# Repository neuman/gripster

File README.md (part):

# Gripster

**A wireless split thumb keyboard that turns your phone into a handheld deck.** Your phone clamps
landscape in the middle on a spring-loaded expanding bridge (Kishi/Backbone style, fits 130–170 mm
phones); two grips flank it and you thumb-type a real 78-key QWERTY on metal snap domes over Bluetooth.

<sub>☝️ **This image is a link — click it to spin the real assembly in 3D, pull it apart with the explode slider, and read the build story.**</sub>

> **Naming, once, so nothing is confusing later:** the project is called **Gripster** in prose. Every
> *internal* identifier — the ZMK board id `thumbdeck`, the board files `thumbdeck_right.kicad_pcb` /
> `thumbdeck_left.kicad_pcb`, the firmware artifact `thumbdeck-zmk.uf2`, the footprint library
> `thumbdeck.pretty/`, and the Bluetooth device name your phone will actually show — is
> **`thumbdeck`**. Those are real strings in real files and they stay as they are.

**What makes this interesting:**

- **It fits your phone, not one phone.** The grips ride a **2-part telescoping tray** (v0.24,
  Abxylute/8BitDo-style): stretch it open, drop the phone in, and two springs clamp it by the short
  edges — ~130 to ~170 mm long, and it collapses flat for a pocket. The phone is held **mechanically** —
  trapped between the tray and **soft TPU grippers with deep capture lips** — so it stays put even
  screen-down over your face like a Switch. **No magnets at all** — v0.25 dropped the secondary MagSafe
  ring: with the spring clamp, the toothed TPU grippers and the deep capture lips all doing their job it
  earned nothing, and its recess was the last thing wanting space in the moving jaw's travel.
- **The back is one flat plane.** v0.25 removed the v0.23 faceted crown and dropped both grips' backs
  to the tray floor, so the grips and the centre tray are coplanar — the device sits flat instead of
  rocking on its tray, and the back halves print straight on the bed with no supports. Every outside
  edge the hands wrap gets a 1.2 mm quarter-round.
- **No switches, no hand-soldering.** 78 Snaptron 7 mm metal snap domes press directly onto gold
  ENIG pads. Every soldered part is SMT on one side of each board — v0.21's pointing nub is a
  single SOT-23-6 hall sensor on the same reflow pass — so JLCPCB builds it 100 % turnkey,
  zero soldering by you.
- **It's not a split.** One certified nRF52840 module in the right grip scans a single 9×10 matrix;
  the left grip carries no active parts, joined by one **20-way** FFC ribbon that carries the matrix
  **and** the cell (v0.27 — the separate battery cable is deleted, so exactly one thing crosses the
  spine). One BLE device, no half-to-half pairing, one battery, one firmware image.
- **The whole product is generated from one Python file.**
  [`hardware/scripts/deck.py`](hardware/scripts/deck.py) emits the KiCad boards, the CadQuery
  shells, the renders *and* the ZMK keymap — so key openings land on dome pads by construction, not
  by luck.
- **The boards are real and finished.** Both PCBs are fully autorouted and DRC-clean in KiCad 9
  (0 violations, 0 unconnected), with the JLCPCB gerber + BOM + CPL package exporting cleanly.

> ### ⚠️ Honest status: designed, not built
>
> **No physical Gripster has ever existed.** Every image *of this device* is a render or a generated
> layout — the only photographs in the repo are of the Rii i8+ that was studied as a reference
> ([`references/`](references/)), alongside the original hand drawings in [`sketches/`](sketches/).
> rev-A (v0.27) is complete on paper: both boards routed and DRC-clean, the fab package
> exports cleanly, all 10 printed parts watertight and bed-fit-checked for an Ender 3 V2. (CI is
> stale — re-run it; the last green build predates the nub module.) Nothing has been ordered, printed, pressed, flashed or typed on.
>
> **Unmeasured and unknown:** ergonomics, dome feel and dome life, BLE range with a phone
> centimetres away and a hand around the antenna, real battery life, and every print tolerance.
> "0 DRC violations" means *no rule was broken*, not *the circuit is correct*.
>
> If you build one, **you are building the first one**. Read
> [Project status & roadmap](#project-status--roadmap) before you spend money.

---

## Table of contents

- [What is this?](#what-is-this)
- [Where to start](#where-to-start)
  - [What's in the repo](#whats-in-the-repo)
  - [Which doc answers which question](#which-doc-answers-which-question)
- [Project status & roadmap](#project-status--roadmap)
  - [Done](#done) · [Not done](#not-done--read-this-before-spending-money) · [Roadmap](#roadmap) · [Open design calls](#open-design-calls) · [Version history](#version-history)
- [FAQ](#faq)
- [Hardware](#hardware)
  - [At a glance](#at-a-glance)
  - [Why a module, not chip-down](#why-a-module-not-chip-down)
  - [Per-grip layout](#per-grip-layout)
  - [The boards, as routed](#the-boards-as-routed)
  - [The 3D model — printable shells + keymats](#the-3d-model--printable-shells--keymats)
  - [Parts list (BOM)](#parts-list-bom)
- [Firmware & software](#firmware--software)
  - [How it works — matrix, GPIO, power, antenna](#how-it-works--matrix-gpio-power-antenna)
  - [Building the firmware](#building-the-firmware)
- [Build guide](#build-guide)
- [Design & generation (the parametric model)](#design--generation-the-parametric-model)
  - [Fabrication view + real KiCad boards](#fabrication-view--real-kicad-boards)
  - [Reproduce the design](#reproduce-the-design)
- [Contributing](#contributing)
- [License](#license)

---

## What is this?

Phones are the most capable computer most people carry and the worst thing to type on. Gripster is a
handheld shell that fixes the input half without replacing the phone: your phone stays the screen
and the compute, and the deck around it becomes the keyboard.

The phone mounts **landscape in the centre**, clamped by two springs against toothed TPU grippers, and it
sits **down inside a well** — deep enough that the glass and the keyboard face form a single flat
plane 14.7 mm off the back. Two contoured grips flank it. You hold it like a game controller and
thumb-type a full split QWERTY: 78 keys on **metal snap domes**, the same clicky stainless discs used
in TV remotes and the [Rii i8+](references/rii8_ref.png), pressed straight onto gold pads on the PCB.
There is no switch, no stem, no solder — the dome *is* the switch. The whole thing takes its design
language from a Game Boy Color: boxy rounded outline, translucent Atomic-Purple shell, dark-gray
keymats. The original concept drawings are in [`sketches/`](sketches/).

Despite the two halves, **this is not a split keyboard**. One certified nRF52840 module lives in the
right grip and scans everything; the left grip holds no active silicon at all — domes, diodes, the
bridge connector, and (v0.27) the cell's plug and its fuse.

```
  LEFT grip (passive)                        RIGHT grip (MCU)
  42 domes + diodes  ── 20-way FFC jumper ──  Ebyte E73 (nRF52840)  ⇄ phone (BLE HID)
  D-pad/OK, mouse       straight type-A       + charger + USB-C + power switch
  LiPo + J4 + F1 PTC    14 matrix + VBAT      scans the whole 9×10 matrix
  (no chip)             + GND, one cable      charges over the same ribbon
```

That means one Bluetooth device to pair, no half-to-half link to drop, one battery to charge, and one
firmware image. The cost is a ribbon cable running through the spine under the phone well — since
**v0.27** that ribbon is 20-way and carries the raw cell alongside the matrix, so it is the *only*
thing crossing, and it is fused at the cell end (**F1**, a 0.75 A PPTC on the left board).

Everything you can see in this repo — the KiCad boards, the printable shells, the renders above, even
the ZMK keymap — is generated from a single parametric Python model,
[`hardware/scripts/deck.py`](hardware/scripts/deck.py). Move a key in the model and the board pad,
the shell opening, the keycap and the firmware matrix transform all move with it.

---

## Where to start

**Just browsing?** Open [the live site](https://neuman.github.io/gripster/) — spin the
model, drag the explode slider, tap the hotspots — then skim [At a glance](#at-a-glance) and the
[FAQ](#faq).

**Thinking about building one?** Read [Project status & roadmap](#project-status--roadmap) first — it
will either talk you out of it or tell you exactly what you are signing up for — then
[`docs/assembly.md`](docs/assembly.md) and
[`docs/fabrication-sourcing.md`](docs/fabrication-sourcing.md).

**Here for the engineering?** [Fabrication view + real KiCad boards](#fabrication-view--real-kicad-boards),
[`docs/routing-status.md`](docs/routing-status.md) and
[`docs/design-decisions.md`](docs/design-decisions.md).

### What's in the repo

| Directory | What's in it |
|---|---|
| [`hardware/scripts/`](hardware/scripts/) | **The source of truth.** [`deck.py`](hardware/scripts/deck.py) is the parametric model; the rest generate boards, fab output, firmware, simulations and 2D renders from it. Old 50-key experiments are archived in [`legacy/`](hardware/scripts/legacy/). |
| [`hardware/kicad/`](hardware/kicad/) | The generated KiCad 9 boards. Nothing here is hand-drawn — see its [README](hardware/kicad/README.md). The JLCPCB fab package builds into `generated/fab/` (a local build artifact, not committed). |
| [`hardware/cad/`](hardware/cad/) | CadQuery 3D: [`deck3d.py`](hardware/cad/deck3d.py) builds the shells and keymats, [`export_full_asm.py`](hardware/cad/export_full_asm.py) builds the nested GLB. Watertight STLs live in [`models/`](hardware/cad/models/). |
| [`hardware/footprints/`](hardware/footprints/) | Custom KiCad footprints, including the [snap-dome contact pad](hardware/footprints/snaptron_7mm_contact_pad.kicad_mod). Some are vendored third-party — see [License](#license). |
| [`hardware/layout/`](hardware/layout/) | [`keymat.json`](hardware/layout/keymat.json), the original sketch digitization. Historical only; the live layout is the `LEGENDS` tables in `deck.py`. |
| [`firmware/zmk-config/`](firmware/zmk-config/) | ZMK v0.3.0 config with a real board definition ([`config/boards/arm/thumbdeck/`](firmware/zmk-config/config/boards/arm/thumbdeck/)) — a unibody board, not a shield, not a split. |
| [`docs/`](docs/) | Eleven engineering documents, plus [`docs/diagrams/`](docs/diagrams/). Table below. |
| [`renders/`](renders/) | Every image in this README, all generated — CAD isometrics from `deck3d.py`, board renders from the `.kicad_pcb`s, and the two hero shots captured from the live viewer. [`history/`](renders/history/) keeps the superseded iteration log. |
| [`sketches/`](sketches/) · [`references/`](references/) | The original concept drawings, and Rii i8+ reference photos used during the design. |
| [`.github/workflows/`](.github/workflows/) | The self-contained ZMK build that produces `thumbdeck-zmk.uf2`. |

### Which doc answers which question

| I want to know… | Read |
|---|---|
| Why is it built this way? Every decision, with rejected alternatives | [`docs/design-decisions.md`](docs/design-decisions.md) |
| How do I actually assemble one, in order, without bricking it? | [`docs/assembly.md`](docs/assembly.md) |
| What do I buy, from whom, for how much? | [`docs/fabrication-sourcing.md`](docs/fabrication-sourcing.md) · [`docs/bill-of-materials.md`](docs/bill-of-materials.md) |
| How does the 9×10 matrix work, and why one diode per key? | [`docs/matrix-and-diodes.md`](docs/matrix-and-diodes.md) |
| Battery, charging, USB, ESD, the FFC bridge | [`docs/connectivity-and-power.md`](docs/connectivity-and-power.md) |
| How does a Python file turn into a routed PCB? | [`docs/routing-status.md`](docs/routing-status.md) |
| How does a Python file turn into printable shells? | [`docs/cad-process.md`](docs/cad-process.md) |
| What would an EE tear apart in a review? | [`docs/design-review.md`](docs/design-review.md) · [`docs/evaluation.md`](docs/evaluation.md) |
| What did we learn from cutting up a Rii i8+? | [`docs/reference-notes.md`](docs/reference-notes.md) |
| What does the architecture look like as a diagram? | [`docs/diagrams/`](docs/diagrams/) |

---

## Project status & roadmap

**rev-A (v0.27). Designed to the point of being orderable. Never built.**

### Done

| | |
|---|---|
| Both PCBs | Fully placed and **autorouted**, **0 DRC violations / 0 unconnected items** (KiCad 9, `kicad-cli 9.0.9`, error severity; both boards re-routed and re-verified for **v0.27**'s 20-way bridge, in the same commit that regenerated them — right board 75 nets / 114 footprints / 30 GND escape vias, left board 60 nets) |
| Fab package | 4-layer gerbers + JLC-format BOM + CPL export cleanly to `hardware/kicad/generated/fab/` via `gen_fab.py`; the exporter refuses to run unless DRC is clean. (That directory is a build artifact and is **not committed** — regenerate it, see [Reproduce the design](#reproduce-the-design).) |
| BOM | Every part real, LCSC-stocked and machine-placeable; no hand-soldered components |
| 3D | 221 bodies assembled and collision-checked at **every clamp position** (`deck3d.py --check` → 0 impossible overlaps at 130 / nominal / 170 / 179 mm open, cable enclosure sealed at each); all 6 shell parts (incl. the v0.21 nub spring + cap) + 2 TPU grippers + 2 keymats fit a 220 × 220 mm Ender 3 V2 bed (204 mm brim-safe limit) |
| Matrix proof | `sim_matrix.py` proves the full 78-key matrix is ghost-free with a diode per key |
| Firmware | Real ZMK v0.3.0 board definition; keymap and matrix transform generated from the model. CI last built green on 2026-07-15, **before the v0.21 nub module — re-run the workflow to validate the current design**. Never flashed; no hardware exists. |

### Not done — read this before spending money

| | |
|---|---|
| **Physically built** | **Never.** Zero boards ordered, zero shells printed, zero domes pressed, zero flashes. Every image of the device is a render. |
| Ergonomics | The grip shape, key pitch and thumb reach have never been tested by a human hand. v0.19 already reshaped the grips once on print-test feedback — expect more. |
| Dome feel & life | Snaptron force curve, keymat living-hinge fatigue and dome retention are *specified* but unmeasured. Fatigue-test a 3×3 keymat coupon before printing a full one. |
| Circuit correctness | Autorouted and DRC-clean is not the same as reviewed. No board has been powered, and no net has been probed. |
| RF | The antenna sits centimetres from a phone and inside a closing hand. Range loss is expected and unquantified. |
| Battery life | Never measured. The ~450–500 mAh cell and ZMK's sleep behaviour suggest weeks of light use; treat that as an estimate, not a spec. |
| Tolerances | Boss travel, screw-boss fit and lid gaps have only been checked in CAD, never against a real print. |
| **FFC route into the ZIF** | **Built in v0.27**, after turning out never to have existed. With the ZIF slot facing the spine there was only **1.20 mm of x** between the slot and a solid grip wall in which to lose **6.74 mm of z** — no route, in any version, for either cable, because both were drawn as straight boxes reaching neither connector. J2 now faces **inboard**: the ribbon folds in the grip's open back cavity and leaves through a low **stepped** duct (z −0.8 .. 2.6 on the grip side, .. 1.95 through the shroud so its roof keeps 1.42 mm) that passes *under* the phone-retention structure (all of which sits at z ≥ 3.9) rather than severing it. The descent clears the matrix diodes by **0.98 / 1.03 mm**, asserted against the real placement. `deck3d.py --check-lanes` sweeps the ribbon's full 21 mm section along the path and exits non-zero if any of it is buried. |

### Roadmap

1. **First article.** Order 5 sets, print the shells, build one, and write down everything that is
   wrong.
2. **Bring-up.** SWD-flash the bootloader, load the UF2, prove the matrix grip-by-grip, measure
   current draw and BLE range with a phone in the well and a hand on the grips.
3. **rev-B**, driven by whatever the first article teaches. Already parked for it: shoulder buttons,
   a canted/fanned key arc, and an I²C trackpad on the TP6–8 breakout.

### Open design calls

Decisions that are **yours to make** — they change the shape of the build:

1. **Feel.** Keys are **rectangular 8.5 × 7 mm at 10 × 9 mm pitch** (v0.17, i8+ chiclet — wider than
   tall so the 6-row field stays short). Still an open call: a flat ortho grid vs a **canted/fanned
   arc** to feel more like a controller — the arc is a keymat/standoff change, not a pitch change.
2. **Phone-fit window.** v0.24's expanding clamp fits phones with a **130–170 mm long edge** (cased)
   out of the box — the springs take up the rest. The jaw itself opens to **179 mm**: it has to
   clear the capture hooks to let the largest phone in, and v0.24e found that until then the travel
   was exactly the phone range, so a 170 mm phone couldn't physically be fitted. The nominal
   near-flush point is tuned to the
   **S25 Ultra + a 1.2 mm case**; `phone_span_min/max` (and `phone_t`/`case_t` for the recess depth)
   re-set the range and re-generate the shells (one command; boards unaffected).
3. **Cell size — settled in v0.18:** standard **403040 (~450–500 mAh)** in the left grip cavity (the
   only standard shape that fits the 5.1 mm free depth there); PROG's 196 mA ≈ 0.43 C suits it as-is.
   Sleep-managed runtime is still weeks.
4. **Shoulder buttons** for index fingers (offload thumb modifiers)? A rev-B matrix change.
5. **Trackpad** — dropped from v1 (single-maintainer ZMK driver + ATI tuning burden); the labelled
   I²C breakout (TP6–8) keeps a rev-B trackpad possible.

### Version history

<details>
<summary><strong>v0.16 → v0.20 changelog</strong> (click to expand)</summary>

- **v0.16 — the shell splits.** The one-piece shells (which needed a 350-class printer) become
  **five printed parts**: two back halves joined at mid-spine with printed tabs + wall shiplaps (no
  seam screws), two grip lids, and a screwed-on center panel that bridges the seam. Everything now
  prints flat on a 220 × 220 mm Ender 3 V2 bed.
- **v0.16-follow (2026-07-15).** A **Rii-style 2u Enter** ends the right grip's H-row — `H J K L +
  ENT`. The `'` key gave up its spot (`'` is now **FN+`;`**), bringing the total to **78 keys**. The
  right board was regenerated and rerouted (still 0/0), the fab package re-exported, **debossed
  keycap legends** added to the keymat model, and the shell screws modelled in the 3D assembly.
- **v0.17 — Rii proportions.** The grips take the Rii i8+'s proportions: **97 mm** tall, a chin cut,
  the E73 + entire power front-end moved up into the **top zone** (the old trackpad space) with the
  ceramic antenna pointing **up off the top board edge**, and **rectangular 8.5 × 7 mm keys** at
  10 × 9 mm pitch replacing the round ones. Boards became 79.5 × 97.0 mm.
- **v0.18 — the phone sinks.** A real **S25 Ultra in a thin case** drops into a **well in the center
  panel** so its **screen surface is flush with the lids' keyboard face** — one 14.7 mm-high front
  plane, and the device drops from 22.9 mm to **15.7 mm** thick overall. That left no cell height in
  the spine, so the **battery moved to the left grip's cavity**: a standard **403040 (~450–500 mAh)**
  under the passive PCB. No board change, no reroute. The FFC minimum length rose accordingly.
- **v0.19 — Game Boy Color rework.** From print-testing feedback: the grip outline goes
  **GBC-boxy** — the parabolic outer cheek bow is deleted (it blocked thumb reach to the
  edge-adjacent keys) and boards narrow **79.5 → 75.0 mm**; corners tuck to r8 (top, antenna-pinned)
  and r11 + a 1.0 mm **crown** (bottom). All 14 face screws become **M3×10 countersunk, flush with
  the face**. The phone well gets **closing end walls** (no more open slots into the grips) and the
  thumb scallop becomes a **watertight curved finger dish**. Shells render and export in
  **translucent Atomic Purple** with dark-gray keymats. Both boards re-routed from scratch against
  the new outline, still 0 violations / 0 unconnected.
- **v0.20 — mirrored modifiers.** A thumb can't cross the phone gap, so Ctrl/Shift/Alt now exist on
  **both** grips: two right-grip caps relabel (`AltGr`→`Alt`, the corner `\`→`Ctrl`) and both grips
  end in the identical stack — Ctrl at the bottom-outside corner, Shift above it, Alt beside Space.
  `\` and `|` move to **FN+`]` / FN+`[`** (direct bindings). Right grip emits RCTRL/RSHFT/RALT.
  **No sticky keys — all chords are plain holds.** Zero PCB change: the matrix transform regenerated
  byte-identical; keymats re-debossed; `sim_matrix` re-run — 78 keys, 0 collisions, PASS.

</details>

---

## FAQ

**Will it fit my phone?**
Out of the box, no — the well is dimensioned for a **Samsung S25 Ultra (77.6 × 162.8 × 8.2 mm bare)
in a ~1.2 mm thin case**, and the fit is tight by design because the screen has to sit flush. But the
phone is four numbers in the model (`phone_w`, `phone_h`, `phone_t`, `case_t` in
[`hardware/scripts/deck.py`](hardware/scripts/deck.py)); change them, re-run the 3D generator, and
you get shells for your phone. **The PCBs are unaffected** — only the printed parts change. Two
caveats: the grip separation is
derived straight from the cased phone envelope — a substantially **larger** phone pushes the grips
further apart than is comfortable to thumb-type across (a smaller one brings them closer, which is
fine ergonomically, you just get less screen). A large change also moves the FFC bridge connectors
apart, so re-check the ribbon length in [`docs/assembly.md`](docs/assembly.md) before ordering.

**Can I build one today?**
You can order everything today — the boards are routed, DRC-clean and the JLCPCB package exports with
one command. But you would be building the **first one that has ever existed**, and rev-A has never
been electrically or ergonomically validated. If that is appealing,
[`docs/assembly.md`](docs/assembly.md) is written to be followed literally, and the one thing to
check first is E73 module stock (JLC **C356849**) — it has been observed swinging from ~1000 units to
~20 in days.

**Is it a split keyboard?**
It looks like one and isn't. There is a **single 9×10 matrix** scanned by one MCU: the right grip
owns COL0–4 locally, the left grip's COL5–9 arrive over a **20-way** FFC ribbon (14 of its conductors
are the matrix and have not changed since rev-A; v0.27 put the battery on the spare ones), and all nine rows are
shared. In ZMK terms it's a **unibody board**, not `CONFIG_ZMK_SPLIT`. One device pairs to your
phone, one battery, one firmware. A useful debugging consequence: a dead **column** on the left
points at the ribbon; a dead **row** kills the same row on *both* grips.

**Why a module instead of a bare nRF52840?**
Because chip-down means owning a 2.4 GHz impedance match and VNA tuning, **FCC/IC/RED radiated
certification**, crystals, a USB bootloader and a from-scratch Zephyr board port. The Ebyte
E73-2G4M08S1C retires all of that, is stocked in JLCPCB's library so it machine-places, and still
breaks out far more GPIO than the 19 matrix pins + 1 battery ADC this design uses. Full reasoning in
[`docs/design-decisions.md`](docs/design-decisions.md) and
[below](#why-a-module-not-chip-down).

**Why no trackpad?**
It was designed in and then deliberately **cut from v1**: a maintained ZMK driver plus ATI/sensitivity
tuning is a large burden for a single maintainer, and it competed for the exact board area the module
and power front-end now occupy. Pointing since v0.21 is the right-grip **hall-effect nub**
(rate-control, ThinkPad-style) — which now lives on the very I²C breakout (**TP6–8**) that was
reserved for a rev-B trackpad — plus the left D-pad with FN-layer mouse keys as fallback. And the
user verdict behind the nub choice: trackpad-style thumb pointing means constantly lifting the
finger; a velocity-controlled nub doesn't.

**What's the battery life?**
Unknown — nothing has been measured. The design carries a standard **403040 LiPo (~450–500 mAh)** in
the left grip, charged at ~196 mA by an MCP73831, with battery percentage reported over BLE. A BLE HID
keyboard with a sleeping nRF52840 should give weeks of light use; that is an expectation based on
comparable ZMK builds, not a number from this device.

**Why ZMK and not QMK?**
ZMK is built around BLE and low-power sleep on nRF52 parts, which is exactly this device's whole job,
and it gives layers, combos and mouse keys for free. The repo pins **ZMK v0.3.0** (the last
HWMv1-compatible release, Zephyr 3.5) and ships a **real board definition** at
[`firmware/zmk-config/config/boards/arm/thumbdeck/`](firmware/zmk-config/config/boards/arm/thumbdeck/)
rather than a shield — the keymap and matrix transform are generated from the same model as the PCB,
so they cannot drift apart.

**What printer do I need?**
Anything with a **220 × 220 mm bed** — the 5-part shell split exists specifically so everything fits
an Ender 3 V2, and `deck3d.py --all` gates every part against a 204 mm brim-safe limit. Largest part
is a back half at 170.5 × 103.8 mm. Shells print in **PETG**; the keymats need **TPU 95A** (or a
tough resin) for the living hinges.

**Do I have to solder?**
No. Every soldered component is on one side of each board and is placed by JLCPCB, 100 % turnkey.
Your hands do four things: press the 78 domes onto their pads under retention tape, seat the FFC
ribbon, print and screw together the shell, and tape in the battery. The one unavoidable exception is
a **one-time SWD flash** of the Adafruit nRF52 bootloader via test pads TP1–5 (possibly preceded by
`nrfjprog --recover`) — that needs a debug probe, and it is the single most likely place a builder
gets stuck. After that it's drag-and-drop UF2 forever.

**What will it cost?**
The **~$150–250 for 5 sets** figure quoted below is **boards + JLCPCB assembly only**. It excludes
domes, retention tape, the LiPo, FFC jumpers, M3 hardware, filament, a debug probe,
shipping and any import duty. Re-quote at order time.

**Can I buy one?**
No. This is an open-source design, not a product — there is no kit, no store and no waiting list.
It's Apache 2.0, so you are free to build it, modify it or sell it yourself.

---

## Hardware

### At a glance

| | value |
|---|---|
| Form | phone (**130–170 mm long edge**) held **LANDSCAPE** in a **2-part telescoping tray** (v0.24, Abxylute/8BitDo-style — spring clamp, TPU edge grippers + deep capture lips; v0.25 no magnets); two dome-key grips, **printed shell** in **Game-Boy-Color design language** (translucent Atomic-Purple shells, dark-gray keymats; v0.25 flat one-plane back with rounded outer edges; every part fits an Ender 3 V2 bed) |
| Keys | **78 Snaptron 7 mm snap domes** (right 36, left 42) · **rectangular 8.5 × 7 mm keys** (i8+ chiclet feel) at **10 × 9 mm** pitch (~1.5–2 mm walls → PETG-printable) · one-piece living-hinge keymat with a **2u space bar**/side + a Rii-style **2u Enter** ending the right H-row · debossed keycap legends |
| Left grip | QWERT-half (6×6) + a **Ø24 integrated D-pad** (v0.25, Rii i8+ style: four arm sectors + a Ø9 centre OK behind one round lid aperture, over the same five domes) + **mouse L/R** buttons — **no active parts**: diodes + the FFC ZIF, plus (v0.27) the cell's JST-PH **J4** and its **F1** PPTC fuse in the chin |
| Right grip | YUIOP-half (6×6 field; the H-row ends in a Rii-style **2u ENT** — `H J K L + ENT`, with `'` on FN+`;`) + the v0.21 **pointing cluster mirroring the left D-pad cluster** (hall-effect nub at the D-pad mirror, PgUp/PgDn as the mouse-button pair's mirror), plus the module and the whole power front-end |
| Modifiers | **mirrored** (v0.20): Ctrl at each grip's bottom-outside corner, Shift directly above it, Alt beside each Space — a thumb can't cross the phone gap, so every mod+same-side-key chord holds the mod with the opposite thumb (right emits RCTRL/RSHFT/RALT). `\` and `\|` moved to FN+`]` / FN+`[`; **no sticky keys — all chords are plain holds** |
| Controller | **one Ebyte E73-2G4M08S1C** (nRF52840 module, JLC C356849) — certified radio, on-module antenna/crystals, UF2-flashable after a one-time SWD bootloader flash |
| Matrix | single **9 × 10**, `col2row`, one **SOD-323** diode/key on the back, 9× 4.7 kΩ row pull-downs, NKRO best-effort |
| Bridge | **20-pin 1.0 mm FFC ZIF** (v0.27: JUSHUO **AFA07-S20FCC-00**, JLC **C262352**, Extended — same tier as the 16-way it replaces) on each grip's inner edge + a **20-way 1.0 mm type-A (same-side contacts) FFC jumper, length ≥240 mm** (v0.24: the clamp span is variable, so the ribbon carries a rolling service loop). It went 16 → 20 way so **one** cable carries the matrix *and* the battery: 14 matrix conductors (ROW0–8, COL5–9 — **identical to rev-A, so firmware is untouched**), 2× GND, 2× VBAT_CELL and 2 NC guards. Nets are assigned by ribbon geometry, so a straight jumper is correct by construction. **⚠ Do not fit a 16-way ribbon** — a 17.0 mm ribbon floats in the 21.0 mm housing with 4.0 mm of slop at *each* end |
| Grip boards | **75.0 × 97.0 mm** each (v0.19: GBC-boxy straight outer edge — the parabolic cheek bow is gone for thumb reach), **4-layer** (sig / GND plane / sig / sig), 1.6 mm FR-4, **ENIG** (mandatory — dome contacts) |
| Power | **LiPo 403040 (4.0 × 30 × 40, ~450–500 mAh) with an integrated PCM — a hard requirement, not a preference** — in the LEFT grip cavity under its PCB (v0.18 — the sunken phone well leaves no cell height in the spine). **v0.27:** it plugs into **J4** (JST-PH) ~8 mm away *in the same grip*, through **F1** (0.75 A hold / 1.5 A trip PPTC) in series with cell +, and reaches the right grip over the bridge ribbon — the separate 2-wire power cable is deleted. **MCP73831** charger + **USB-C** + inline **USBLC6-2** ESD + **MSK12C02 power switch** + **reset tact** (pinhole) + **charge LED** stay in the right grip; the charger is still on the cell side of the switch, so it charges while switched off |
| Pointer | v0.21/22: **ThinkPad-style hall-effect nub** on the right grip, Ploopy-Bean architecture — a TMAG5273 I²C hall sensor (SOT-23-6, machine-placed) reads a magnet in a printed flexure spring **through the PCB**; true **rate-control** firmware (deflection → cursor velocity, quadratic curve) in an in-tree Zephyr module on the repurposed TP6–8 I²C breakout. The mount is a **standard 4.4 mm-square TrackPoint platform**: wear the printed **red soft-dome replica** or any **genuine classic TrackPoint cap**. FN+D-pad mouse keys remain as fallback |
| Wireless | BLE HID; USB-C for charging + UF2 flashing |
| Fabrication | **JLCPCB** turnkey, **two separate orders** (right + left), single-sided reflow (**all SMT on the back**, single-pass — v0.21 adds no THT) → rough target **~$150–250 for 5 sets**, boards + assembly only (re-quote at order time) |
| Firmware | **ZMK v0.3.0**, real board definition `thumbdeck` (unibody, not a split); the CI workflow is a **self-contained** ZMK v0.3.0 build producing `thumbdeck-zmk.uf2` |

### Why a module, not chip-down

> A bare nRF52840 would force you to own a 2.4 GHz match + VNA tuning, **FCC/IC/RED radiated
> certification**, a USB bootloader, crystals, and a from-scratch Zephyr board port. A pre-certified
> module retires all of that and still breaks out far more GPIO than the 19 matrix pins + battery
> sense this design needs. We use the **Ebyte E73** because it's stocked in the JLCPCB library and
> machine-places — see [`docs/fabrication-sourcing.md`](docs/fabrication-sourcing.md). Full decision
> record in [`docs/design-decisions.md`](docs/design-decisions.md).

Everything below is generated from one parametric model
([`hardware/scripts/deck.py`](hardware/scripts/deck.py)) — regenerate with the
[pipeline](#reproduce-the-design).

### Per-grip layout

6-col grid of rectangular 8.5 × 7 mm keys at 10 × 9 mm pitch per grip (bottom row = a 2u space bar;
the right H-row ends in a Rii-style 2u Enter — `H J K L + ENT`, `'` on FN+`;`), plus the cluster
features. The E73 + power front-end sit in the top zone with the antenna up off the top edge;
PgUp/PgDn sit beside the pointing nub as the mouse-button pair's mirror (v0.21).

### The boards, as routed

Rendered straight from the committed `.kicad_pcb` files — this is the copper that would be
fabricated, not a concept drawing.

<details>
<summary><strong>Show both boards, front and back</strong> (click to expand)</summary>

**Front — right grip.** Nothing but snap-dome contact pads (centre pad + leg ring with the routing
escape gap) and front-layer traces. The front carries **zero soldered parts**; the domes are pressed
on later, under retention tape.

**Back — right grip.** Everything soldered lives here: a diode behind every dome, the Ebyte module
(**antenna-up at the top edge**, v0.17), charger, USB-C, ESD, power switch, reset tact, charge LED,
the FFC connector and all passives — the whole cluster in the top zone, which is what let the chin
be trimmed.

**Left grip, front and back.** No active silicon at all — 42 domes, 42 diodes, the FFC ZIF, and
(v0.27) the cell's JST-PH **J4** and its **F1** PPTC fuse in the chin.

</details>

Inside the centre tray, v0.24d gives the contents a **lane plan** — as of **v0.27** it reads
`spring | FFC | spring` front to back (the power lane went with the cable it carried), every lane on
one z with printed divider ribs between them, so nothing is stacked over anything and the ribbon
sits inside the *moving* shroud's cavity — enclosed at every extension, not just while the fixed
tray happens to still be underneath. The FFC lane widened with the connector — 17.0 → **21.0 mm** on
y **28.5** — and y 40.0…82.5 inside the cavity is now free.

### The 3D model — printable shells + keymats

Fit-checked in CAD against real-dimension component models — datasheet heights, not a physical
build. The mechanical parts are generated from the **same** parametric
model as the PCB ([`hardware/scripts/deck.py`](hardware/scripts/deck.py)) via CadQuery, so key
openings land on dome pads and bosses land on mount holes *by construction*. The whole stack — back
halves (the right one is the grip **and** the fixed tray in a single part since v0.25), PCB with
**real-dimension** components (E73 module, USB-C, connectors, SOT-23s, 0402s, snap-domes), LiPo, FFC
jumper, keymats, grip lids, **TPU grippers**, phone — is assembled in one frame and
**collision-checked at every clamp position**: `deck3d.py --check` reports **0 impossible overlaps**
at 130 mm, nominal, 170 mm and 179 mm fully open, with the cable enclosure sealed at each.
Full method: [`docs/cad-process.md`](docs/cad-process.md).

**Exploded** — back halves (right = grip + tray, one part) · PCB + domes · keymats · grip lids · TPU grippers · phone:

The shell prints flat on a **220 × 220 mm Ender 3 V2 bed** — the old one-piece shells needed a
350-class printer. Since **v0.24** the rigid center panel is gone: the two back halves are the
**grips themselves** — `back_right` is the fixed ground, `back_left` is the moving clamp jaw — and
since **v0.25** the telescoping tray is printed as *part of* `back_right` rather than bolted on, with
the left grip's inner shroud lapping inside it to enclose the springs and the single FFC. The tray
top is an uninterrupted flat phone rest; **TPU grippers** on each inner edge do the mechanical hold.
Opening the left grip's five screws services the battery. v0.17
keymats carry the **rectangular keycaps** (8.5 × 7 rounded-rect plungers, 18.5 mm 2u caps for the
space bars and the right H-row's Rii-style Enter, round cluster keys) on the same living-hinge web
(TPU 95A), now with **debossed Rii-style legends** (primary, shifted-symbol and FN-layer); the grip
lids get matching rounded-rect openings. v0.25 replaces the left grip's five separate nav buttons
with **one Ø24 integrated D-pad** — four arm sectors and a Ø9 centre OK, split by 2.0 mm relief
moats, through a single dished Ø24.4 lid aperture. The five domes underneath do not move, so no
board or firmware changes; the presses stay discrete because the web is **thinned to 0.4 mm under
each moat** and pinned all the way round the pad by a **clamp ring** on the lid backed by a **rib**
on the mat.
Part sizes: back halves 170.5/162.8 × 103.8 mm, grip lids 77.9 × 103.8, keymats ~63 × 86–89 — all
within the 204 mm brim-safe limit.

Back half (grip + tray) | Grip lid | TPU gripper | Keymat
:---:|:---:|:---:|:---:
 |  |  | 

Regenerate: `hardware/cad/.venv/bin/python hardware/cad/deck3d.py --all --check --render`
(`--all` also gates every part on the Ender 3 V2 bed-fit; `--sync-models` refreshes the tracked STLs
in [`hardware/cad/models/`](hardware/cad/models/)).

**Full nested assembly** —
[`hardware/cad/models/thumbdeck_full_asm.glb`](hardware/cad/models/thumbdeck_full_asm.glb) is the
whole build as one glTF file with a **named object tree** (open it in Blender or any glTF viewer, or
spin it in the browser on [the live site](https://neuman.github.io/gripster/), which
loads a web-optimized build of this same file): translucent **Atomic-Purple** shells + dark-gray keymats (real glTF PBR
materials), **KiCad-generated boards** (real Edge.Cuts body + routed copper + soldermask + silkscreen
from the `.kicad_pcb`s), every placed component and snap dome as its real-dimension body, plus the
403040 battery, FFC jumper (drawn as a straight box in its tray lane — its descent into the ZIFs is
the open item in [Not done](#not-done--read-this-before-spending-money)), the M3 shell screws and the
flush-mounted cased phone. All transforms are baked into the vertices, so the tree survives even
minimal TRS-only viewers. Regenerate:
`hardware/cad/.venv/bin/python hardware/cad/export_full_asm.py`.

### Parts list (BOM)

Full BOM in [`docs/bill-of-materials.md`](docs/bill-of-materials.md) — regenerated from the
machine-exported `fab/*/bom.csv`. **78 keys**, **one** module, **one** battery. Everything soldered is
placed by JLC; your hands do domes, shell, battery and the FFC jumper.

#### Core

| Item | Part | Qty | Notes |
|---|---|---|---|
| Snap dome | **Snaptron 7 mm 4-leg dome** (SnapForce series) | 78 (+spares) | Pressed onto ENIG contact pads under retention tape — no solder. Footprint: [`snaptron_7mm_contact`](hardware/footprints/snaptron_7mm_contact_pad.kicad_mod) (centre pad + leg ring with routing escape gap). |
| Dome retention | Snaptron taped polyimide array (Peel-N-Place) **or** 0.2–0.3 mm laser-cut polyimide spacer | 2 | **Required** — the keymat alone won't stop a dome walking off its contact ring. The tape channels also vent the domes. |
| Keymat | one-piece 3D print, **TPU 95A** / tough resin | 2 | Living-hinge strips; fatigue-test a coupon >10 k cycles before the full mat. |
| Diode | **1N4148WS SOD-323** (JLC **C2128**, Basic) | 78 | One/key, `col2row`, cathode band → row net, **on the back**. Basic part = free feeder. |
| **Controller** | **Ebyte E73-2G4M08S1C** (nRF52840, JLC **C356849**) | **1** | Certified radio, on-module antenna/crystals. On the **back** of the right grip, **antenna-up at the top board edge** (v0.17 — farthest from the centred phone/LiPo, off the edge the palm doesn't cradle). Extended + X-ray + **volatile stock** (seen swinging ~1000 → ~20 units in days) — reserve/backorder before anything else. |
| **LiPo** | **403040 pouch (4.0 × 30 × 40 mm, ~450–500 mAh)** with an **integrated PCM — REQUIRED**, JST-PH pigtail | 1 | The protection module is a hard requirement, not advice: overcurrent 2.0–2.5 A / 8–16 ms, overcharge 4.275 V, overdischarge 2.75 V. It and **F1** cover *different* bands and neither alone is sufficient. v0.18: foam-taped (0.3 mm) to the **LEFT grip's floor under its PCB** — the sunken phone well displaced it from the spine. **v0.27:** the pigtail plugs into **J4** ~8 mm away in the *same* grip instead of running a ~265 mm bare lead across the whole device. **Meter pigtail polarity against the "+"/"−" silk at J4 — on the LEFT board — before first plug-in** (pin 1 = "+"); vendors wire PH pigtails both ways. |
| **Bridge** | **AFA07-S20FCC-00** **20**-pin 1.0 mm FFC ZIF (JLC **C262352**) ×2 + **20-way 1.0 mm FFC jumper, TYPE-A ONLY (contacts on the SAME side at both ends), length ≥240 mm** | 1 set | Bottom-contact, 2.5 mm tall, slide lock, side entry, 0.3 mm FFC. Type-A is load-bearing — the left grip's nets are assigned by ribbon geometry, so a straight jumper matches 1:1. **v0.27: buy 20-way. A 16-way ribbon is dangerous here** — 17.0 mm floats in the 21.0 mm housing with 4.0 mm of slop at *each* end, i.e. up to a 4-position shift. The conductor order (GND, GND, ROW0–8, COL5–9, NC, VBAT_CELL, VBAT_CELL, NC, index 0 = highest deck y) is chosen so even a 4-position shift lands VBAT on a **column** — one dead MCU pin — rather than on GND, which is a dead short across the cell. **v0.24:** the clamp span is variable, so the ribbon carries a rolling service loop that pays out as the jaw slides; it must reach at max extension (~195 mm J2-to-J2) plus the fold, so coupon-tune the loop radius. |
| **Fuse (F1)** | **Bourns MF-MSMF075-2** PPTC, 1812 (JLC **C84140**) | 1 | **v0.27, safety-critical.** 0.75 A hold / 1.5 A trip, 13.2 V, Imax 100 A, R<sub>init</sub> ≤ 0.45 Ω. On the **LEFT** board at deck (50.0, 5.5), in series with cell **+** between **J4** and **J2** — it must be on the **cell** side of the ribbon or it protects nothing. Why it exists: the ribbon now carries the raw cell, and a 1.0 mm-pitch FFC conductor (0.70 × 0.035 mm = 0.0245 mm²) hits its 105 °C insulation limit around 2.8 A·√s and melts its own PET in ~0.2 s at a real short, while the cell's PCM does not trip until 2.0–2.5 A. The **0.43–2.0 A band in between** — the signature of a partially abraded conductor in a mechanism that flexes on every phone insertion — is covered by nothing else. Cost is **charge time**, not capacity: the 0.45 Ω moves CC→CV handover to a lower cell voltage so the taper is longer; undercharge at termination is I<sub>TERM</sub> × R<sub>loop</sub> ≈ 10–16 mV, negligible against the MCP73831's own ±32 mV VREG tolerance. |

#### Power / USB front-end (right grip unless noted — required even with a module)

| Item | Part | Qty | Notes |
|---|---|---|---|
| Charger IC | **MCP73831T-2ACI/OT** (JLC **C424093**) | 1 | Module has no charger. PROG = 5.1 kΩ → ~196 mA (~0.43 C of the 403040 cell). Don't sub -2ATI (different Vreg). 4.7 µF 0805 at **both** VDD and VBAT per datasheet. |
| USB-C receptacle | **fully-SMD 16P** (JLC **C165948**) + **2× 5.1 kΩ** CC1/CC2 | 1 | Must be SMD — a THT shell breaks 100 % reflow. Missing CC = never charges. |
| ESD array | **USBLC6-2SC6** (JLC **C7519**) **inline** between USB-C and module | 1 | |
| Power switch | **MSK12C02** slide (C431540) between cell+ and VBAT | 1 | Charger stays on the cell side — it charges while switched off. Knob through a slot in the **top** shell wall (v0.17 moved the electronics cluster to the top zone). v0.27: cell + arrives here as **VBAT_CELL over the bridge ribbon**; the switch gates only the load, so the ribbon is live whenever the cell is plugged into J4. |
| Reset button | **TS-1187A** tact (C318884), top-actuated | 1 | Pressed through a 1.6 mm pinhole in the shell floor — UF2 double-tap without opening the shell. |
| Charge LED | 0603 red (C2286) + 1 kΩ | 1 | On MCP73831 STAT; visible through a 1.5 mm floor hole. |
| Battery connector | **JST-PH 2.0 mm side-entry SMT** (S2B-PH-SM4-TB, C295747) — **J4, on the LEFT board** | 1 | Polarized; the hobby-LiPo standard. **v0.27:** it moved grips. Deck (60.0, 5.5) in the left grip's chin, mouth facing +y, so the 403040 plugs in ~8 mm from where it lives; the old right-board **J3 is deleted**. It is also the only way to de-energize the ribbon for service, since the power switch gates the load, not the cell. Pin 1 = "+". |
| Battery sense | 2× 1 MΩ divider (÷2) + 100 nF SAADC filter | 1 | On P0.02/AIN0. |
| SWD pads | **TP1–5** (SWDIO / SWDCLK / RESET / 3V3 / GND), silk-labelled | — | One-time bootloader flash / recovery. TP6–8 = the nub sensor's live I²C (SDA/SCL/INT), still probe-able. |

#### Matrix hardening (on the board)

| Item | Part | Qty | Notes |
|---|---|---|---|
| Row pull-downs | 4.7 kΩ 0402 (R1–R9) | 9 | External at the MCU — the nRF's internal pull is too weak over the ribbon. |

Column series resistors and a dome-field TVS were considered and **dropped** — the bridge is a short
fixed internal ribbon, not a long flexing cable. Note them as a rev-B option if field ESD issues
appear.

#### PCB / hardware

| Item | Spec | Qty | Notes |
|---|---|---|---|
| PCB | `thumbdeck_right` + `thumbdeck_left`, **4-layer**, 1.6 mm FR-4, **ENIG** | 5 each | Two distinct boards, **two separate JLC orders**. Fab package exported by `gen_fab.py` into `hardware/kicad/generated/fab/`. |
| Shell | **v0.25: 6 prints** (`back_right` = grip **+ fixed tray in one part**, `back_left`, 2 grip lids, nub spring + cap) + 2 **TPU grippers** | 1 | Retention is entirely mechanical (TPU grippers + capture lips + spring clamp) — no magnets. All parts fit a 220 × 220 bed. |
| Pointing nub | **TMAG5273A1** hall sensor (C3716049, on the right board) + **Ø4 × 2 mm N45 disc magnet, axially magnetized** (supermagnete **S-04-02-N**) in the printed spring | 1 + spare magnets | v0.21: the only added electronics is one SOT-23-6 — machine-placed with everything else. v0.22: the spring's post is a standard TrackPoint square platform — genuine classic caps fit; a red soft-dome replica prints in TPU. **v0.26:** the magnet is now a real body in the CAD (it had only ever been a *hole*) and sits a measured **3.33 mm from the hall element** — not the 2.6 mm the old comment claimed, which was the distance to the outside of the chip package rather than to the sensing element 0.73 mm inside it. The flexure was re-derived against the TrackPoint IV spec and **kept at 0.8 mm** (thickening it would have made the nub nearly rigid); what it gained was a **root fillet** at the arms' square T-junction — where every model put peak stress — and a **0.35 mm plunge stop**, without which pressing harder sped the cursor up at constant tilt. Grade is N45, **not** N52: N52 tops out at 65 °C and the loss is irreversible. |
| M3 hardware | **M3×10 countersunk** screws + M3 heat-set inserts (Ø4.0 bores) | 10 + 10 | Heads flush with the face (v0.19). 5 per grip lid, and that is all of them: v0.24 deleted the 4 center-panel screws, and v0.25 deleted the tray's own 2 by printing it as part of `back_right`. |

---

## Firmware & software

### How it works — matrix, GPIO, power, antenna

- **One matrix, not a split.** A single 9×10 matrix scanned by one module. Right grip = COL0–4
  (local); left grip = COL5–9 (over the ribbon); ROW0–8 shared. This is a ZMK **unibody** board —
  *not* `CONFIG_ZMK_SPLIT`. [`docs/matrix-and-diodes.md`](docs/matrix-and-diodes.md).
- **GPIO:** 19 matrix pins + 1 battery ADC, plus a spare I²C (SDA/SCL/INT) broken out to test pads
  TP6–8 for a rev-B trackpad. COL9 sits on P0.04/AIN2 — the XTAL pins (P0.00/P0.01) are deliberately
  kept free.
- **Power electronics all in the right grip:** cell → charger (cell side) → **power switch** → VBAT →
  the module's VDDH — topology unchanged. The cell itself sits in the LEFT grip (v0.18), and since
  **v0.27** its whole path is `cell → J4 → F1 (PPTC) → J2 → ribbon → right board`: the connector and
  the fuse are on the left board, and **VBAT_CELL crosses on the bridge ribbon** instead of on a
  separate 2-wire cable. So the bridge carries power as well as logic, and the ribbon is live
  whenever the cell is plugged in — the switch gates only the load. VBAT_SENSE (R22/R23/C6 → AIN0)
  is unchanged.
- **Antenna:** the E73's ceramic antenna points **up, off the top board edge** (v0.17 — centre-top,
  farthest from the phone/LiPo and off the edge the palm doesn't cradle), with an all-layer keep-out
  crossing the edge and a 0.6 mm relief in the shell wall. Expect the phone + hand to detune range
  somewhat; re-check on the first article.

A block diagram lives in [`docs/diagrams/`](docs/diagrams/). Every other document is indexed in
[Which doc answers which question](#which-doc-answers-which-question).

### Building the firmware

- **Config:** [`firmware/zmk-config/`](firmware/zmk-config/), pinned to **ZMK v0.3.0** — the last
  HWMv1-compatible release (Zephyr 3.5).
- **Board, not shield:** [`config/boards/arm/thumbdeck/`](firmware/zmk-config/config/boards/arm/thumbdeck/)
  is a real ZMK board definition (`thumbdeck.dts`, `thumbdeck.keymap`, `thumbdeck_defconfig`, …)
  describing a **unibody** keyboard. The matrix transform and keymap in there are *generated* by
  `gen_firmware.py` from the same model as the PCB, so a key cannot exist on the board and be missing
  in the firmware.
- **CI:** [`.github/workflows/build.yml`](.github/workflows/build.yml) is a **self-contained** build
  (deliberately not ZMK's reusable `build-user-config` workflow, which assumes the config sits at the
  repo root — ours lives under `firmware/zmk-config/`). It runs
  `west build -s zmk/app -p always -b thumbdeck` and uploads the result as the artifact
  **`thumbdeck-zmk-uf2`**, containing `thumbdeck-zmk.uf2`.
- **Locally:** `cd firmware/zmk-config && west init -l config && west update && west zephyr-export`,
  then the same `west build` line with
  `-DZMK_CONFIG="$PWD/config"`.
- **Status:** the firmware **compiles green in CI** (a ≈137 KB `thumbdeck-zmk.uf2` was produced on
  2026-07-15). It has never been flashed to hardware, because no hardware exists. Compiling is not
  working.

---

## Build guide

Path: **order boards (turnkey, no routing left to do) → press domes → print shells + keymats →
assemble + FFC jumper → battery → first flash → pair.** Full detail in
[`docs/assembly.md`](docs/assembly.md).

> Nobody has executed these steps. They are derived from the design, not transcribed from a build.

### Step 1 — Order the boards

Nothing is left to route: both boards are **DRC-clean and fully routed**, and the JLCPCB package is
one `gen_fab.py` run away.

1. Upload `hardware/kicad/generated/fab/right/thumbdeck_right_gerbers.zip` + `bom.csv` +
   `positions.csv` as one JLCPCB PCBA order, and the `fab/left/` set as a **second, separate order**
   (two different designs — panelizing them costs more than it saves). That directory is a build
   artifact and is not committed; regenerate it with
   [the pipeline](#reproduce-the-design) (`python3 hardware/scripts/gen_fab.py`).
2. Options: **4-layer**, 1.6 mm FR-4, **ENIG** (snap domes need gold — HASL oxidises within weeks of
   cycling), assembly side = **bottom**, single-sided. The right board needs **Standard** assembly
   (the E73 is Extended + X-ray); the left board (42 diodes + the ZIF + v0.27's J4 and F1) can go Economic.
3. **Check the DFM preview before paying** — LED polarity (the classic JLC 180° flip), SOT-23-5/6
   rotation, USB-C and E73 orientation. Rotate in the preview if needed.
4. Rough target **~$150–250 for 5 sets** — **boards + assembly only**; costing detail and part
   numbers in [`docs/fabrication-sourcing.md`](docs/fabrication-sourcing.md); re-quote at order time.
   **E73 stock is volatile** (observed from ~1000 down to ~20 units within days) — check
   jlcpcb.com/parts for **C356849** and **reserve/backorder the modules before anything else**.

### Step 2 — Domes, retention, keymat

- Press the **78 Snaptron domes** onto the gold pads under the **polyimide retention tape/array**
  (pockets locate each 7 mm dome; the tape channels vent them).
- Print the **shells** (PETG) and the **keymat** (TPU 95A); validate boss travel + hinge fatigue on a
  3×3 coupon **before** committing the full mat.

### Step 3 — Assemble

- Everything soldered arrives soldered — there is **no hand-soldering step**.
- **FFC jumper first** (the ZIFs hide under the lids): **≥240 mm, 20-way, type-A** ribbon between the
  two ZIF connectors, **contacts facing the board at both ends** (bottom-contact ZIFs); flip the
  latches closed. **Ribbon before the cell, always** — since v0.27 two of its conductors are the raw
  cell, so seating it with the battery plugged in is a live operation. Then seat the ribbon into its
  tray lane.
- **Battery first (v0.18):** foam-tape the 403040 to the LEFT grip's floor before the left board goes
  in — the cell lives UNDER the left PCB, and since **v0.27** its pigtail reaches **J4 on that same
  board**, so nothing has to be routed across the spine. Then seat each board on its 3 support posts
  + perimeter bosses; screw on each grip lid
  (5 × M3×10 CSK). Route the FFC through the tray — which since v0.25 is already part of
  `back_right`, so there is nothing to bolt — lap the left grip's inner shroud into it, then press
  the TPU grippers on. The battery is serviced by opening the left grip. v0.24d: the ribbon threads its
  **own walled channel** with a spring in each outboard lane (**v0.27:** `spring | FFC | spring` —
  the power lane is gone) — thread it before the shrouds are lapped together, and don't let the
  service loop sit across a divider rib. Full order:
  [`docs/assembly.md`](docs/assembly.md).
- **Battery:** meter the pigtail against the **"+"/"−" silk at J4 — on the LEFT board** (pin 1 = "+")
  first (vendors wire PH pigtails both ways) — but **do not connect the cell until after the first
  flash** (REGOUT0 must be programmed first — see [`docs/assembly.md`](docs/assembly.md)). Slide
  switch OFF for assembly. Use a cell with an **integrated PCM**; **F1** on the left board covers the
  band the PCM does not, and neither substitutes for the other.

### Step 4 — First flash, pair

- The E73 ships **blank**. One-time step: SWD-flash the **Adafruit nRF52 bootloader (nice_nano
  build)** via TP1–5 (a `nrfjprog --recover` may be needed first). The bootloader sets
  REGOUT0 = 3.3 V. **This step needs a debug probe** and is the most likely place to get stuck.
- From then on it's UF2: double-tap reset (pinhole) → drag the CI-built `thumbdeck-zmk.uf2` on.
- **Pair:** the host pairs to a device advertising as **"thumbdeck"** (that is the literal
  `ZMK_KEYBOARD_NAME` in the board definition — not a typo for Gripster). No inter-half pairing. Type
  across both grips — a dead **column** on the left → suspect the ribbon seating; a dead **row** hits
  **both** grips (rows shared). Confirm battery % over BLE.

---

## Design & generation (the parametric model)

### Fabrication view + real KiCad boards

The generated boards are **real, routed, DRC-clean KiCad 9 files** —
[`hardware/kicad/generated/thumbdeck_right.kicad_pcb`](hardware/kicad/generated/thumbdeck_right.kicad_pcb)
(36 domes + 36 diodes + module + power front-end; 75 nets, 114 footprints) and
[`thumbdeck_left.kicad_pcb`](hardware/kicad/generated/thumbdeck_left.kicad_pcb) (42 + 42, no active
parts, 60 nets since v0.27 added J4 and F1) —
**0 DRC violations, 0 unconnected items** on both (`kicad-cli 9.0.9`, error severity; both boards
re-routed and re-verified for v0.27's 20-way bridge). The full fab package (4-layer
gerbers, JLC-format BOM + CPL) exports to `hardware/kicad/generated/fab/`; the exporter refuses to
run unless DRC is clean. Routing is fully autonomous — Freerouting + a GND stitcher + a DRC gate; see
[`docs/routing-status.md`](docs/routing-status.md).

Three placement constraints moved with the wider connector, and they are frozen: `deck.py`'s
inner-mid M3 mount hole went from `board_h × 0.42` (40.74) to a fixed **46.0** — its Ø8 boss disc was
the only thing capping the connector's pin count — and **J2 moved from deck y 24.5 to 28.5** on both
boards, because the 21 mm ribbon would otherwise overlap the clamp's front spring lane. J2's land is
26.85 mm long with 4.08 mm to the boss (the gate is 4.00). **VBAT_CELL/VBAT now route at 0.4 mm** via
a real power netclass injected in `route.sh`'s DSN rewrite; before v0.27 `gen_board.py`'s `PWR = 0.5`
was dead code and VBAT_CELL shipped at 0.2 mm — ~336 mΩ, a third of the whole charge loop.

*Caveat worth stating plainly: 0 DRC violations means no design rule was broken. It does not mean the
circuit is correct, and no board has ever been powered.*

Like the i8+: the **front** carries only the snap-dome contact pads and front-layer traces; the
**back** carries everything soldered — the 78 diodes, the Ebyte module, charger, USB-C, ESD, power
switch, reset tact, charge LED, FFC connectors, passives. All parts on one side makes the SMT job
**single-sided** (one stencil, one pass) and **100 % turnkey** — there are no hand-soldered parts.
The USB-C shell's plated stakes and the FFC/slide-switch locating pegs are the only through-board
features, and they are all placed in the same single-pass JLC assembly.

### Reproduce the design

```bash
cd hardware/scripts
python3 gen_board.py                  # placement + netlist + deterministic USB copper + GND escape vias
./route.sh right && ./route.sh left   # Freerouting autoroute -> GND stitch + zone fill -> DRC gate
python3 gen_fab.py                    # gerbers/BOM/CPL per side (refuses to export unless DRC-clean)
python3 verify_alignment.py           # top-to-bottom 2D stack audit: PCB domes/diodes vs model, cap gutters, boss clearances
python3 sim_matrix.py                 # ghosting/NKRO proof (78 keys, 0 collisions) — FINAL PASS
python3 gen_firmware.py               # ZMK transform/keymap/gpio, generated from the model
python3 layout_gen.py --iter 23       # per-grip layout diagram -> renders/iter_23.png
python3 render_fab.py                 # Edge.Cuts + placement fab view -> renders/fab_view.png
# --- 3D (CadQuery; see docs/cad-process.md) ---
cd ../.. && hardware/cad/.venv/bin/python hardware/cad/deck3d.py --all --check --render
hardware/cad/.venv/bin/python hardware/cad/export_full_asm.py   # nested full-assembly GLB (KiCad boards + all parts)
```

Requires Python 3 + `matplotlib`; the board pipeline needs **KiCad 9** (`pcbnew` Python module +
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
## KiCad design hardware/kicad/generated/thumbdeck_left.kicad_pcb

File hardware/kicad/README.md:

# hardware/kicad — generated boards + autonomous fab pipeline (rev-A)

Everything in `generated/` is produced headlessly by the pipeline in
`hardware/scripts/`. **Both boards are fully routed and DRC-clean** (0 violations,
0 unconnected, kicad-cli 9.0.9) and the JLC fab package exports cleanly. Nothing
here is hand-drawn; to change the board, change the model/scripts and regenerate.
**The boards are unbuilt** — nothing here has been fabricated or bring-up tested,
and DRC-clean means no rule is violated, not that the circuit is correct.

## The pipeline

```bash
cd hardware/scripts
python3 gen_board.py                  # placement + full netlist + deterministic USB copper
                                      #   + GND escape vias -> generated/thumbdeck_{right,left}.kicad_pcb
./route.sh right                      # Specctra DSN (In1 marked power, + a 0.5mm `power`
                                      #   netclass for the cell path) -> Freerouting (-Xss16m)
./route.sh left                       #   -> SES import -> stitch.py (GND vias + zone fill) -> DRC -> renders
python3 gen_fab.py                    # gerbers/BOM/CPL per side; REFUSES to export unless DRC is 0/0
python3 sim_matrix.py                 # 78-key matrix ghosting/NKRO proof (final pass)
```

Requirements: **KiCad 9** (`pcbnew` Python module + `kicad-cli`), a Java runtime
and **freerouting.jar**. Note that `route.sh` currently **hardcodes the author's
toolchain paths** for both (the `JAVA=` and `FR=` lines at the top) — edit them to
match your machine before running it. Details and quirks in
[`docs/routing-status.md`](../../docs/routing-status.md).

## What's in `generated/`

| file | what |
|---|---|
| `thumbdeck_right.kicad_pcb` / `thumbdeck_left.kicad_pcb` | routed, DRC-clean 4-layer boards (F.Cu / In1 GND plane / In2 / B.Cu) |
| `thumbdeck_*.kicad_pro/.kicad_prl/.kicad_dru` | project + 0.2 mm rules (via 0.6/0.3) |
| `thumbdeck_*.dsn` / `thumbdeck_*.ses` | Freerouting in/out (local build artifacts — git-ignored, regenerate with `route.sh`) |
| `drc_right.json` / `drc_left.json` | DRC results: **0 violations, 0 unconnected** (error severity) — git-ignored, regenerate with `route.sh` |
| `fab/right/`, `fab/left/` | **the order package**: `thumbdeck_*_gerbers.zip` + `bom.csv` + `positions.csv` (JLC format) — git-ignored, regenerate with `gen_fab.py` |
| `thumbdeck_*_placement.csv` | placement summary (ref, value, x, y, rot, side) |

## Ordering

Two **separate** JLCPCB PCBA orders (right + left — don't panelize two different
designs): 4-layer, 1.6 mm FR-4, **ENIG (mandatory — snap-dome contacts)**, assembly
side **bottom**, Standard assembly for the right board (E73 = Extended + X-ray),
Economic OK for the left. Check the DFM preview for part rotations (LED polarity,
SOT-23s, USB-C, E73). Full walkthrough:
[`docs/fabrication-sourcing.md`](../../docs/fabrication-sourcing.md).

## Notes

- **v0.27 (2026-08-07):** the bridge is a **20-way** 1.0 mm ZIF (JUSHUO
  AFA07-S20FCC-00, LCSC C262352) whose four extra conductors carry the cell across
  the spine, so the separate battery cable is gone. **J3 is deleted from the right
  board**; the left board gains **J4** (JST-PH-2, C295747) and **F1** (Bourns
  MF-MSMF075-2 PPTC, C84140) — so the left board is no longer purely passive, and
  its BOM has two placements it did not have before. J2 sits at deck y 28.5 on both
  boards. Both boards were re-generated and **re-routed to 0/0** with the new parts.
  The `power` netclass injected by `route.sh` is what finally gives the cell path
  its 0.5 mm width; details in
  [`docs/routing-status.md`](../../docs/routing-status.md).
- The boards are frozen build artifacts — regenerate rather than hand-edit; the
  DRC gate in `gen_fab.py` protects the export either way.
- Opening them in the KiCad 9 GUI is fine for inspection; the pipeline does not
  depend on the GUI for anything.

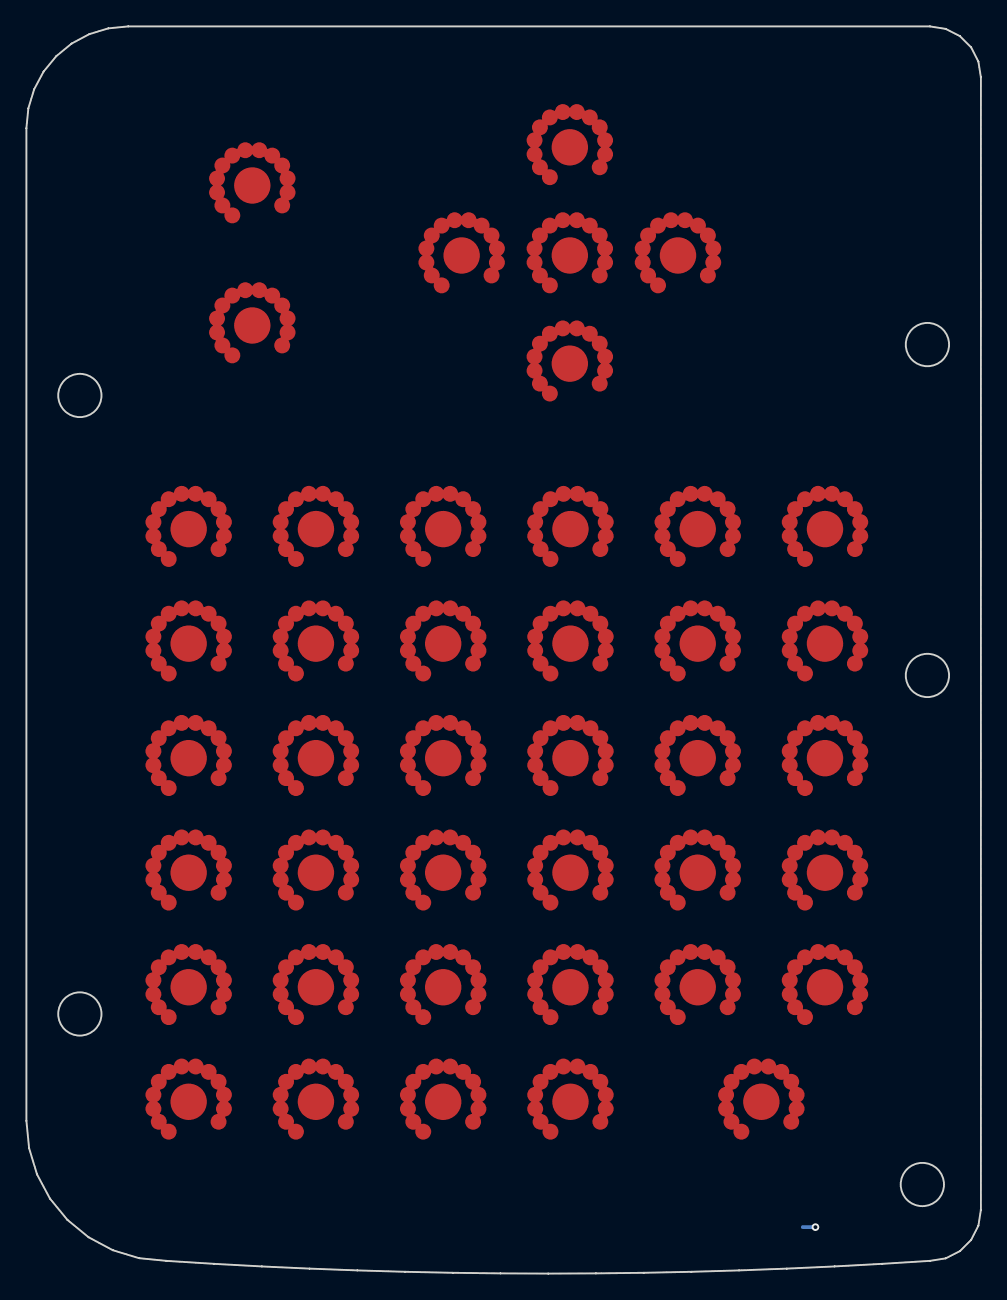
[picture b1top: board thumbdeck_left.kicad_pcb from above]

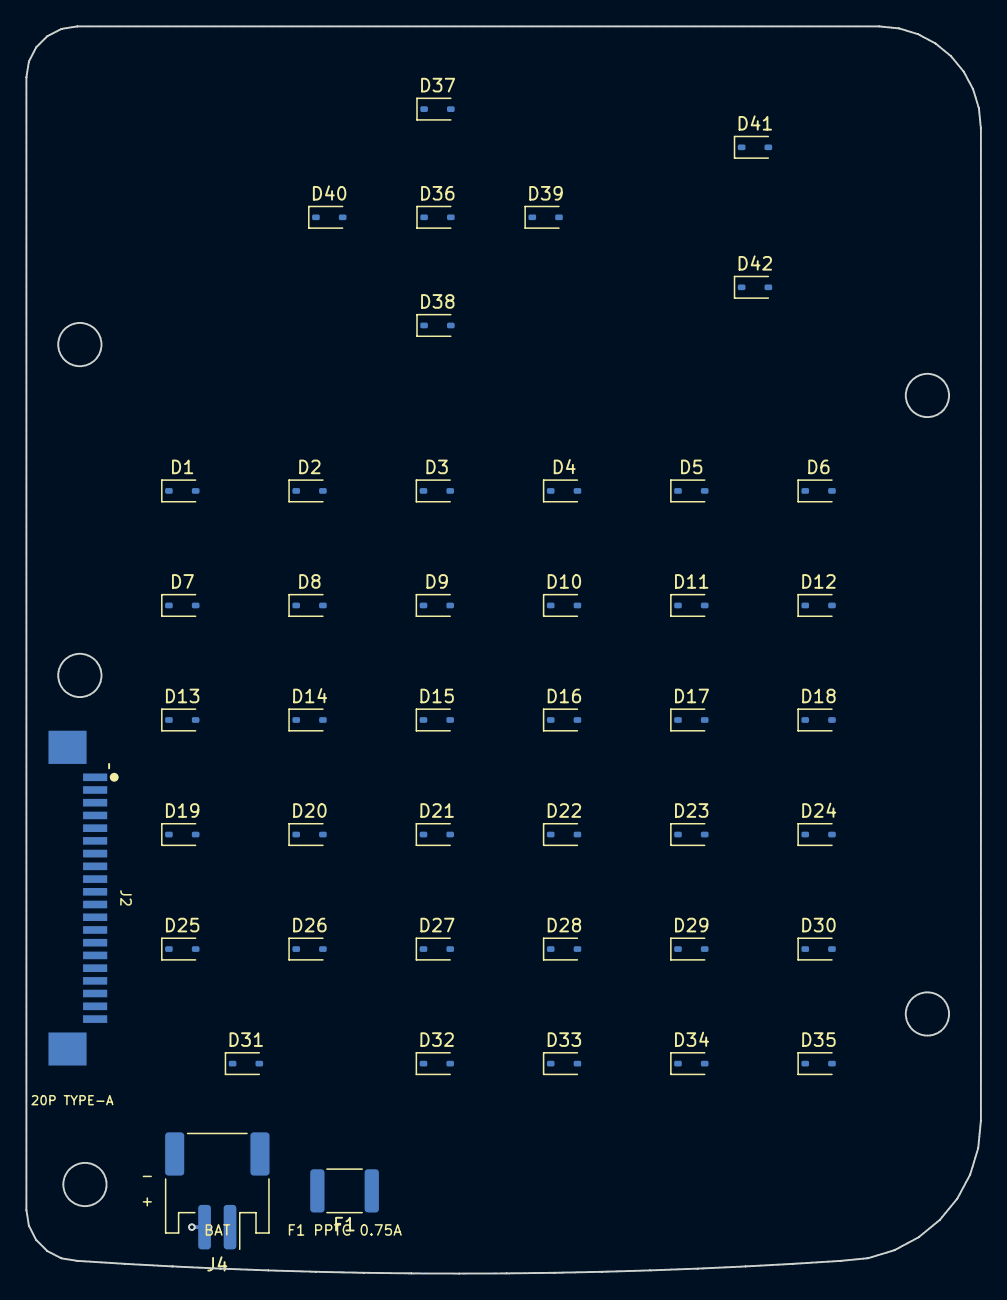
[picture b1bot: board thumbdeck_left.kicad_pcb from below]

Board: 4 copper layers, 75.0 x 98.0 mm, 87 parts (45 on the bottom side), 59 nets.

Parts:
D1, D2, D3, D4, D5, D6, D7, D8, D9, D10, D11, D12, D13, D14, D15, D16, D17, D18, D19, D20, D21, D22, D23, D24, D25, D26, D27, D28, D29, D30, D31, D32, D33, D34, D35, D36, D37, D38, D39, D40, D41, D42: 1N4148WS; D_SOD-323
F1: PPTC-0.75A; Fuse_1812_4532Metric
J2: FFC20; ffc_afa07_s20fcc
J4: JST-PH-2; JST_PH_S2B-PH-SM4-TB_1x02-1MP_P2.00mm_Horizontal
SW1, SW2, SW3, SW4, SW5, SW6, SW7, SW8, SW9, SW10, SW11, SW12, SW13, SW14, SW15, SW16, SW17, SW18, SW19, SW20, SW21, SW22, SW23, SW24, SW25, SW26, SW27, SW28, SW29, SW30, SW31, SW32, SW33, SW34, SW35, SW36, SW37, SW38, SW39, SW40, SW41, SW42: SNAP7; snaptron_7mm_contact

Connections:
COL5: J2.12, SW1.1, SW6.1, SW11.1, SW16.1, SW21.1, SW26.1, SW31.1, SW36.1, SW41.1
COL6: J2.13, SW2.1, SW7.1, SW12.1, SW17.1, SW22.1, SW27.1, SW32.1, SW37.1, SW42.1
COL7: J2.14, SW3.1, SW8.1, SW13.1, SW18.1, SW23.1, SW28.1, SW33.1, SW38.1
COL8: J2.15, SW4.1, SW9.1, SW14.1, SW19.1, SW24.1, SW29.1, SW34.1, SW39.1
COL9: J2.16, SW5.1, SW10.1, SW15.1, SW20.1, SW25.1, SW30.1, SW35.1, SW40.1
DN_L1: D1.2, SW1.2
DN_L2: D2.2, SW2.2
DN_L3: D3.2, SW3.2
DN_L4: D4.2, SW4.2
DN_L5: D5.2, SW5.2
DN_L6: D6.2, SW6.2
DN_L7: D7.2, SW7.2
DN_L8: D8.2, SW8.2
DN_L9: D9.2, SW9.2
DN_L10: D10.2, SW10.2
DN_L11: D11.2, SW11.2
DN_L12: D12.2, SW12.2
DN_L13: D13.2, SW13.2
DN_L14: D14.2, SW14.2
DN_L15: D15.2, SW15.2
DN_L16: D16.2, SW16.2
DN_L17: D17.2, SW17.2
DN_L18: D18.2, SW18.2
DN_L19: D19.2, SW19.2
DN_L20: D20.2, SW20.2
DN_L21: D21.2, SW21.2
DN_L22: D22.2, SW22.2
DN_L23: D23.2, SW23.2
DN_L24: D24.2, SW24.2
DN_L25: D25.2, SW25.2
DN_L26: D26.2, SW26.2
DN_L27: D27.2, SW27.2
DN_L28: D28.2, SW28.2
DN_L29: D29.2, SW29.2
DN_L30: D30.2, SW30.2
DN_L31: D31.2, SW31.2
DN_L32: D32.2, SW32.2
DN_L33: D33.2, SW33.2
DN_L34: D34.2, SW34.2
DN_L35: D35.2, SW35.2
DN_L36: D36.2, SW36.2
DN_L37: D37.2, SW37.2
DN_L38: D38.2, SW38.2
DN_L39: D39.2, SW39.2
DN_L40: D40.2, SW40.2
DN_L41: D41.2, SW41.2
DN_L42: D42.2, SW42.2
GND: J2.1, J2.2, J2.MP, J4.2
ROW0: D1.1, D2.1, D3.1, D4.1, D5.1, J2.3
ROW1: D6.1, D7.1, D8.1, D9.1, D10.1, J2.4
ROW2: D11.1, D12.1, D13.1, D14.1, D15.1, J2.5
ROW3: D16.1, D17.1, D18.1, D19.1, D20.1, J2.6
ROW4: D21.1, D22.1, D23.1, D24.1, D25.1, J2.7
ROW5: D26.1, D27.1, D28.1, D29.1, D30.1, J2.8
ROW6: D31.1, D32.1, D33.1, D34.1, D35.1, J2.9
ROW7: D36.1, D37.1, D38.1, D39.1, D40.1, J2.10
ROW8: D41.1, D42.1, J2.11
VBAT_CELL: F1.2, J2.18, J2.19
VCELL_RAW: F1.1, J4.1

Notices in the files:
README.md:
License:
Licensed under the Apache License, Version 2.0 — see [LICENSE](LICENSE) and [NOTICE](NOTICE).
Copyright © 2026 Eric Neuman.
Licensed under the Apache License, Version 2.0 (the "License");
you may not use this file except in compliance with the License.
You may obtain a copy of the License at
http://www.apache.org/licenses/LICENSE-2.0
Unless required by applicable law or agreed to in writing, software
distributed under the License is distributed on an "AS IS" BASIS,
WITHOUT WARRANTIES OR CONDITIONS OF ANY KIND, either express or implied.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
License: Apache 2.0
